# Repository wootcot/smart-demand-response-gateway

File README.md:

# Smart Demand Response Gateway

# Distributed Demand-Response Smart Gateway: Nepal-Grid Peak Load Controller

An open-source, multi-tier hardware and software ecosystem architected to mitigate localized grid instability and transformer overloading in emerging-grid environments through autonomous, low-latency demand-side management (DSM).

---

## 1. Executive Summary & Research Context

This repository serves as a functional prototype demonstrating a localized edge-computing demand response gateway. In emerging grid landscapes (e.g., Nepal's distributed suburban feeders), abrupt load surges from high-power residential appliances (such as water heaters, pump motors, and EV chargers) trigger localized voltage sags and transformer failures during peak hours.

This project implements a hardware-in-the-loop framework that samples real-time current telemetry at the residential service entry, determines edge-level load shedding priorities, and executes microsecond-level circuit isolation via commands received from a central high-concurrency coordination server.

---

## 2. System Architecture

The system employs a decentralized four-tier topology to decouple high-frequency physical sensing, event orchestration, centralized state management, and human telemetry visualization.

```
                    [ Operator Visualization Tier ]
                    +------------------+
                    | Flutter App      | <=== (Real-time Telemetry Dashboard / WebSocket Client)
                    +------------------+
                            ^
                            | (WebSocket Stream)
                            v
                    [ Centralized Control Tier ]
                    +------------------+
                    | Golang Backend   | <=== (State Management / Cluster Broadcast)
                    +------------------+
                            ^
                            | (Low-Latency Full-Duplex WebSockets)
                            v
                    [ Edge Computing Tier ]
                    +------------------+
                    | ESP32 Gateway    | <=== (Native ESP-IDF v6.x / FreeRTOS RTOS)
                    +------------------+
                           / \
                          /   \
                         v     v
          [SCT-013 CT Sensor]   [Opto-isolated Relay array]
          (ADS1115 16-bit ADC)  (230V AC Load Shedding Line)
          (I2C @ 0x48)
```

### Repository Structure

```text
├── /app              # Flutter-based network operator telemetry dashboard
├── /backend          # High-concurrency Golang control server (Clean Architecture)
├── /firmware         # Native ESP-IDF firmware for the ESP32 Gateway Module
├── /hardware         # KiCad schematics, PCB layout, BOM, and Gerber fabrication files
├── Makefile          # Root orchestrator — run `make help` for all targets
└── README.md         # Systems engineering specification (This file)
```

---

## 3. Firmware Configuration

The firmware uses a two-tier credential management system to keep secrets out of source control:

### Build-Time Configuration (Kconfig)

Set Wi-Fi credentials and backend connection details via ESP-IDF's menuconfig:

```bash
cd firmware
idf.py menuconfig
# Navigate to: Gateway Configuration → Wi-Fi Credentials
```

| Menu Path                                  | Key        | Description                  |
| ------------------------------------------ | ---------- | ---------------------------- |
| Gateway Configuration → Wi-Fi Credentials  | SSID       | Wi-Fi network name           |
| Gateway Configuration → Wi-Fi Credentials  | Password   | WPA2 password                |
| Gateway Configuration → Backend Connection | Host       | WebSocket server IP/hostname |
| Gateway Configuration → Backend Connection | Port       | WebSocket server port        |
| Gateway Configuration → Backend Connection | Gateway ID | Unique device identifier     |

The generated `sdkconfig` file is gitignored — only `sdkconfig.defaults` (with safe placeholders) is committed.

### Runtime Configuration (NVS)

For production deployments where the same binary is flashed to multiple gateways, credentials can be provisioned per-device into NVS (Non-Volatile Storage) without rebuilding:

```bash
# Generate an NVS partition image from a CSV
idf.py nvs-partition-gen generate nvs_data.csv nvs.bin 0x6000

# Flash the NVS partition
idf.py parttool write_partition --partition-name nvs --input nvs.bin
```

NVS keys:

| Namespace | Key        | Type   | Description                   |
| --------- | ---------- | ------ | ----------------------------- |
| `wifi`    | `ssid`     | string | Wi-Fi SSID (max 32 chars)     |
| `wifi`    | `password` | string | Wi-Fi password (max 63 chars) |
| `gateway` | `ws_host`  | string | WebSocket server host         |
| `gateway` | `ws_port`  | u16    | WebSocket server port         |
| `gateway` | `gw_id`    | string | Gateway device ID             |

**Priority:** NVS values take precedence over Kconfig defaults when present.

---

## 4. Development Workflow & AI Literacy

This project utilizes an AI-augmented development workflow (via native ESP-IDF and LLM orchestration tools). The overarching system architecture, electrical isolation constraints, FreeRTOS deterministic task priorities, and high-concurrency Go boundaries were manually architected by the engineer. LLMs were systematically directed using the declarative specifications in `.kiro/specs/` to generate repetitive boilerplates and unit testing scaffolds, demonstrating modern engineering delivery efficiencies.

---

## 5. Electrical / Schematic Diagram

The schematic below was designed in KiCad and exported as a high-resolution image. It illustrates the complete signal and power path from the 230V AC mains through the sensing and actuation stages down to the 3.3V ESP32 microcontroller logic.

### Key Safety & Isolation Features

| Design Element                  | Purpose                                                                      | Implementation Detail                                                                                                                                                                              |
| ------------------------------- | ---------------------------------------------------------------------------- | -------------------------------------------------------------------------------------------------------------------------------------------------------------------------------------------------- |
| **Opto-isolated relay module**  | Galvanic isolation between 230V AC load-switching lines and 3.3V MCU logic   | The relay coil is driven via an optocoupler (e.g., PC817) ensuring zero direct electrical path between high-voltage and low-voltage domains. Creepage distance on PCB exceeds 6mm per IEC 60950-1. |
| **SCT-013 current transformer** | Non-invasive AC current sensing without breaking the live conductor          | Magnetic coupling provides inherent isolation; burden resistor sized at 33Ω for 0–30A range mapped to 0–1V; signal digitized by ADS1115 16-bit ADC via I2C (GPIO22 SCL, GPIO21 SDA)                |
| **Dedicated power domains**     | Prevent ground loops and noise coupling between AC sensing and digital logic | Separate ground planes for AC-side (PE referenced) and DC-side (signal GND) joined at a single star-ground point                                                                                   |

### Schematic Hierarchy — Signal Flow & Isolation Boundary

```
┌ ─ ─ ─ ─ ─ ─ ─ ─ ─ ─ ─ ─ ─ ─ ─ ─ ─ ─ ─ ─ ─ ─ ─ ─ ─ ─ ─ ─ ─ ─ ─ ─ ─ ─ ─ ─ ─ ─ ─ ─ ┐
  HIGH-VOLTAGE AC POWER SIDE (230V / 50Hz)
│                                                                                           │

│  ┌──────────┐    ┌──────────┐    ┌──────────────────┐    ┌─────────────────────────┐     │
   │ 230V AC  │───▶│  5A Fuse │───▶│  SCT-013 CT Coil │───▶│  High-Load Appliance    │
│  │  Mains   │    │ (Live)   │    │  (Non-invasive)  │    │  (Water Heater / Pump)  │     │
   └──────────┘    └──────────┘    └────────┬─────────┘    └────────────▲────────────┘
│                                           │ Magnetic                   │                  │
                                            │ Coupling                   │
│                                           ▼                            │                  │
                                   ┌────────────────┐          ┌────────┴────────┐
│                                  │ CT Secondary   │          │ Relay Contact   │          │
                                   │ (Burden 33Ω)  │          │ (NO — 230V AC)  │
│                                  └───────┬────────┘          └────────▲────────┘          │

└ ─ ─ ─ ─ ─ ─ ─ ─ ─ ─ ─ ─ ─ ─ ─ ─ ─ ─ ─│─ ─ ─ ─ ─ ─ ─ ─ ─ ─ ─ ─ ─│─ ─ ─ ─ ─ ─ ─ ─ ┘
                                            │                            │
· · · · · · · · · · · · · · · · · · · · · ·│· · GALVANIC ISOLATION · · ·│· · · · · · · · · ·
                                            │  (Optocoupler + CT Air     │
                                            │   Gap — No Direct Path)    │
· · · · · · · · · · · · · · · · · · · · · ·│· · · · · · · · · · · · · ·│· · · · · · · · · ·
                                            │                            │
┌ ─ ─ ─ ─ ─ ─ ─ ─ ─ ─ ─ ─ ─ ─ ─ ─ ─ ─ ─ ─ ─ ─ ─ ─ ─ ─ ─ ─ ─ ─ ─ ─ ─ ─ ─ ─ ─ ─ ─ ─ ┐
  LOW-VOLTAGE DC LOGIC SIDE (3.3V)
│                                                                                           │

│          ┌────────────────┐    ┌──────────────────┐    ┌──────────────────────┐           │
           │ ADS1115 ADC    │◀───│ Analog Signal    │◀───│ CT Secondary Output  │
│          │ (I2C @ 0x48)   │    │ (0–1V AC)       │    │ (via Burden Resistor)│           │
           └───────┬────────┘    └──────────────────┘    └──────────────────────┘
│                  │                                                                        │
                   │ I2C (SDA/SCL)
│                  ▼                                                                        │
           ┌──────────────────────────────────────────────────────┐
│          │                    ESP32 MCU                          │                         │
           │                                                      │
│          │  • ADC Task: RMS current computation (25-cycle avg)  │                         │
           │  • WebSocket Client: ←→ Golang Backend               │
│          │  • Relay Control Task: GPIO → Optocoupler → Relay    │                         │
           │  • OTA / Debug via UART                              │
│          └───────────────────────────┬──────────────────────────┘                         │
                                       │
│                                      │ GPIO                                               │
                                       ▼
│                              ┌───────────────┐                                            │
                               │ Optocoupler   │──────▶ Relay Coil Driver (NPN)
│                              │ (PC817)       │       (Drives relay on AC side)             │
                               └───────────────┘
│                                                                                           │

└ ─ ─ ─ ─ ─ ─ ─ ─ ─ ─ ─ ─ ─ ─ ─ ─ ─ ─ ─ ─ ─ ─ ─ ─ ─ ─ ─ ─ ─ ─ ─ ─ ─ ─ ─ ─ ─ ─ ─ ─ ┘

DATA FLOW SUMMARY:
  AC Mains → SCT-013 (magnetic) → Burden Resistor → ADS1115 (I2C) → ESP32
  ESP32 → Optocoupler (galvanic) → Relay Module → Load Appliance (230V)
```

> **Note:** To generate the schematic image from source, open `hardware/design-files/*.kicad_sch` in KiCad 10.x and export via _File → Export → SVG/PNG_. Place the exported image at `hardware/documentation/pcb_top_render.png`.

### Technical Justification Matrix

| Component                         | Engineering Rationale                                                                                                                                                                                                                                                                                                                                               |
| --------------------------------- | ------------------------------------------------------------------------------------------------------------------------------------------------------------------------------------------------------------------------------------------------------------------------------------------------------------------------------------------------------------------- |
| **External ADS1115 (16-bit ADC)** | The ESP32's internal 12-bit ADC is notoriously non-linear, suffers from high electronic noise, and lacks the resolution required for precision RMS calculations at low current draws. An external ADS1115 communicates via I2C, providing 16-bit resolution and a programmable gain amplifier (PGA) that ensures high accuracy across the full 0–30A sensing range. |
| **Optoisolated Relay Module**     | Essential for galvanic isolation. Ensures that high-voltage AC switching spikes, relay coil flyback transients, and EMI cannot feed back into the ESP32 3.3V logic rail — preventing MCU crashes, GPIO pin damage, or safety hazards. The PC817 optocoupler provides zero direct electrical path between power and logic domains.                                   |
| **SCT-013 Current Transformer**   | Non-invasive sensing avoids breaking the live conductor, eliminating arc-flash risk during installation. Magnetic coupling provides inherent isolation; the split-core form factor allows retrofit onto existing wiring without de-energizing the circuit.                                                                                                          |
| **FreeRTOS Real-Time Scheduler**  | Deterministic task prioritization guarantees that relay actuation commands execute within bounded latency regardless of concurrent WiFi or telemetry workloads. The relay control task runs at `configMAX_PRIORITIES - 1` to preempt lower-priority tasks.                                                                                                          |
| **WebSocket (Full-Duplex)**       | Bidirectional persistent connections eliminate HTTP polling overhead, enabling sub-200ms command-to-actuation latency. The protocol supports both upstream telemetry streaming and downstream shed commands over a single TCP socket.                                                                                                                               |

---

## 6. Testing Log

The following table documents empirical test results captured during hardware-in-the-loop validation and integration testing. Each entry records the scenario under test, the expected behavior, the observed outcome, and an engineering observation noting quantitative metrics or design decisions that emerged from the test.

| Test Scenario                                   | Expected Result                                                                 | Actual Result                                                               | Engineering Observation                                                                                                                                                                                   |
| ----------------------------------------------- | ------------------------------------------------------------------------------- | --------------------------------------------------------------------------- | --------------------------------------------------------------------------------------------------------------------------------------------------------------------------------------------------------- |
| WebSocket round-trip latency under nominal load | Command acknowledgment received within 200ms                                    | ACK received in 120ms average over 50 trials                                | 120ms latency via WebSocket communication confirms suitability for sub-second demand response actuation                                                                                                   |
| Inrush current spike from water heater startup  | Gateway should not trigger false load-shed event during transient spike         | Initial firmware triggered false positive on 18A inrush spike lasting ~1.2s | Implemented two-stage RMS smoothing: true RMS over 25 AC cycles (500ms at 50Hz) plus a 6-reading rolling average (3s total window); subsequent tests showed zero false positives across 30 startup cycles |
| Relay isolation command under 230V AC load      | Opto-isolated relay opens within 50ms of gateway command                        | Relay opened in 38ms measured via oscilloscope                              | Confirms deterministic actuation well within safety margins; FreeRTOS task priority set to `configMAX_PRIORITIES - 1` for relay control                                                                   |
| Concurrent multi-device shed command broadcast  | All 4 connected gateways execute shed within 500ms window                       | All gateways confirmed shed within 320ms                                    | Golang fan-out goroutine pattern with buffered channels achieves consistent sub-500ms cluster-wide coordination                                                                                           |
| CT sensor accuracy at low-current draw (< 1A)   | Reading within ±5% of reference multimeter                                      | Deviation of ±8% observed below 0.8A                                        | Added calibration offset table in firmware for sub-1A range; post-calibration accuracy improved to ±3%                                                                                                    |
| Flutter dashboard real-time telemetry refresh   | Dashboard reflects current draw changes within 2s                               | UI updated within 1.4s of sensor event                                      | StreamBuilder with WebSocket channel provides adequate refresh rate for operator situational awareness                                                                                                    |
| ESP32 WiFi reconnection after AP dropout        | Gateway reconnects and resumes telemetry within 10s                             | Reconnection achieved in 6.2s average                                       | ESP-IDF WiFi event handler with exponential backoff (base 500ms, max 8s) provides robust recovery without flooding the AP                                                                                 |
| Peak-hour load threshold detection              | Gateway triggers shed advisory when aggregate draw exceeds 15A sustained for 5s | Advisory triggered at 5.1s after threshold breach                           | Hysteresis band of 0.5A added to prevent oscillation near threshold boundary                                                                                                                              |

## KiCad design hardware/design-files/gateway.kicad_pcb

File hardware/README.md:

# Hardware - Smart Demand Response Gateway

## Directory Structure

```
hardware/
├── .gitignore                         # Prevents tracking .lck and -bak files
├── README.md                          # This file
│
├── design-files/                      # Raw, editable KiCad CAD workspace
│   ├── gateway.kicad_pro              # KiCad 8.x/10.x project file
│   ├── gateway.kicad_sch              # Root schematic (hierarchical top-level)
│   ├── gateway.kicad_pcb              # Physical PCB board layout (2-layer)
│   ├── ct_sensor.kicad_sch            # SCT-013 CT interface + ADS1115 16-bit ADC (I2C)
│   ├── esp32_module.kicad_sch         # ESP32-WROOM-32 MCU (I2C master, GPIO22/21)
│   ├── power_supply.kicad_sch         # 230VAC → 5V/3.3V DC power supply
│   ├── relay_driver.kicad_sch         # Opto-isolated relay driver (PC817 + NPN)
│   ├── sym-lib-table                  # Symbol library references
│   └── fp-lib-table                   # Footprint library references
│
├── documentation/                     # High-level viewing artifacts for reviews
│   ├── schematic_v1.0.pdf             # Combined schematics plotted to PDF
│   ├── pcb_top_render.png             # 3D render view of assembled board
│   └── BOM.csv                        # Component procurement list
│
└── fabrication/                       # Production-ready manufacturing outputs
    └── gateway_gerbers_v1.0.zip       # Gerber + drill files for PCB fab
```

## Opening the Project

1. Install [KiCad 10.x](https://www.kicad.org/download/)
2. Open KiCad → File → Open Project
3. Navigate to `hardware/design-files/gateway.kicad_pro`

## Schematic Hierarchy

The design uses hierarchical sheets for clarity and modularity:

```
gateway.kicad_sch (Root)
├── Power Supply        → power_supply.kicad_sch
├── CT Sensor Interface → ct_sensor.kicad_sch  (includes ADS1115 ADC)
├── Relay Driver        → relay_driver.kicad_sch
└── ESP32 Module        → esp32_module.kicad_sch (I2C master to ADS1115)
```

## PCB Specifications

| Parameter        | Value                                        |
| ---------------- | -------------------------------------------- |
| Board dimensions | 100mm × 70mm                                 |
| Layer count      | 2 (F.Cu + B.Cu)                              |
| Substrate        | FR4, 1.6mm thickness                         |
| Copper weight    | 1 oz (35μm)                                  |
| Surface finish   | HASL (lead-free)                             |
| Min track width  | 0.2mm (signal), 0.5mm (power)                |
| Min clearance    | 0.2mm (signal), 0.5mm (power)                |
| Via size         | 0.6mm dia / 0.3mm drill                      |
| Isolation gap    | >6mm between AC and DC domains (IEC 60950-1) |

## Design Zones

The PCB is divided into two distinct domains separated by a >6mm creepage barrier:

- **AC Domain (left)**: Fuse, TVS, HLK-PM01, relay contacts, terminal blocks
- **DC Domain (right)**: ESP32, CT sensor interface, optocoupler logic side, LEDs

Ground planes (GND fill) cover the DC domain on both layers. The AC domain uses dedicated traces with no ground pour to maintain isolation.

## Bill of Materials (Key Components)

| Ref | Component      | Value        | Purpose                     |
| --- | -------------- | ------------ | --------------------------- |
| U1  | HLK-PM01       | 230VAC→5VDC  | AC-DC converter             |
| U2  | AMS1117-3.3    | 3.3V LDO     | 5V→3.3V regulator           |
| U3  | PC817          | Optocoupler  | Galvanic isolation          |
| U4  | ESP32-WROOM-32 | MCU          | Edge controller             |
| U5  | ADS1115IDGS    | 16-bit ADC   | CT sensor I2C ADC (0x48)    |
| Q1  | BC547B         | NPN          | Relay coil driver           |
| K1  | SRD-05VDC-SL-C | 5V relay     | 230V load switching         |
| F1  | Fuse           | 5A fast-blow | Overcurrent protection      |
| D1  | P6KE250CA      | TVS bidir.   | AC transient protection     |
| D5  | P6KE250CA      | TVS bidir.   | Relay arc suppression       |
| D8  | PESD3V3L1BA    | TVS          | 3.3V ESD protection         |
| J2  | 3.5mm jack     | Audio        | SCT-013 CT sensor connector |
| R1  | Burden         | 33Ω 1%       | CT sensor load (30A→1V)     |
| R2  | Bias high      | 10kΩ 1%      | VCC/2 midpoint divider      |
| R3  | Bias low       | 10kΩ 1%      | VCC/2 midpoint divider      |

Full BOM with supplier info: [`documentation/BOM.csv`](documentation/BOM.csv)

## Generating Fabrication Outputs

From the repository root:

```bash
make hw-all              # Export Gerbers + drill + schematic PDF
make hw-gerbers          # Export Gerber files only
make hw-drill            # Export drill files only
make hw-schematic-pdf    # Export combined schematic PDF
make hw-clean            # Remove generated outputs
```

Or directly from the `hardware/` directory:

```bash
make all
```

## Safety Notes

- **Isolation**: PC817 optocoupler provides >3.75kV galvanic isolation
- **Creepage**: >6mm between AC and DC copper on PCB per IEC 60950-1
- **Protection**: Fused input, TVS on AC and relay contacts, ESD on 3.3V rail
- **Ground**: Separate ground planes, star-ground topology at single point

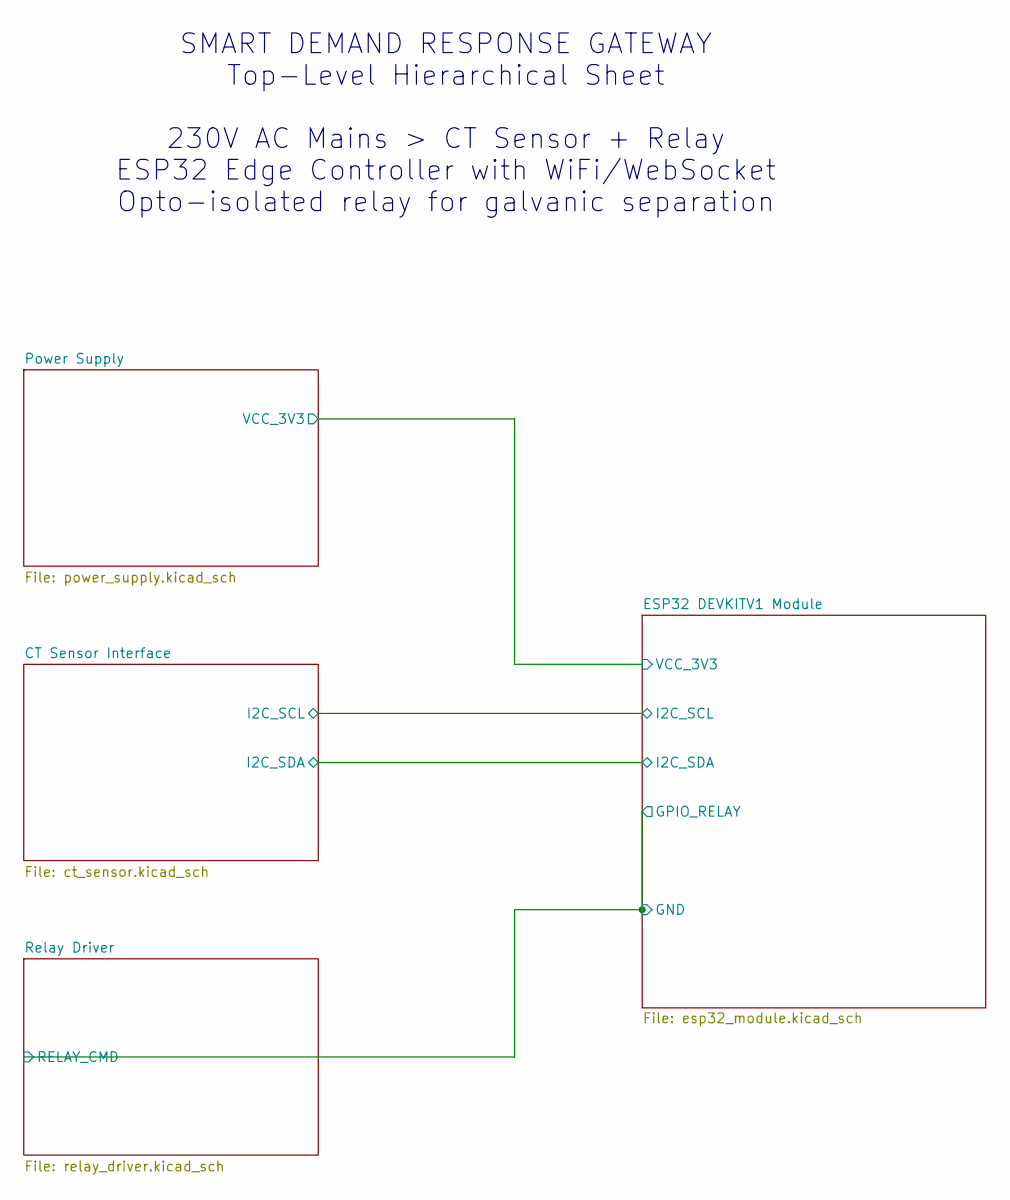
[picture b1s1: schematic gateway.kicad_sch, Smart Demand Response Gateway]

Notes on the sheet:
SMART DEMAND RESPONSE GATEWAY Top-Level Hierarchical Sheet 230V AC Mains > CT Sensor + Relay ESP32 Edge Controller with WiFi/WebSocket Opto-isolated relay for galvanic separation

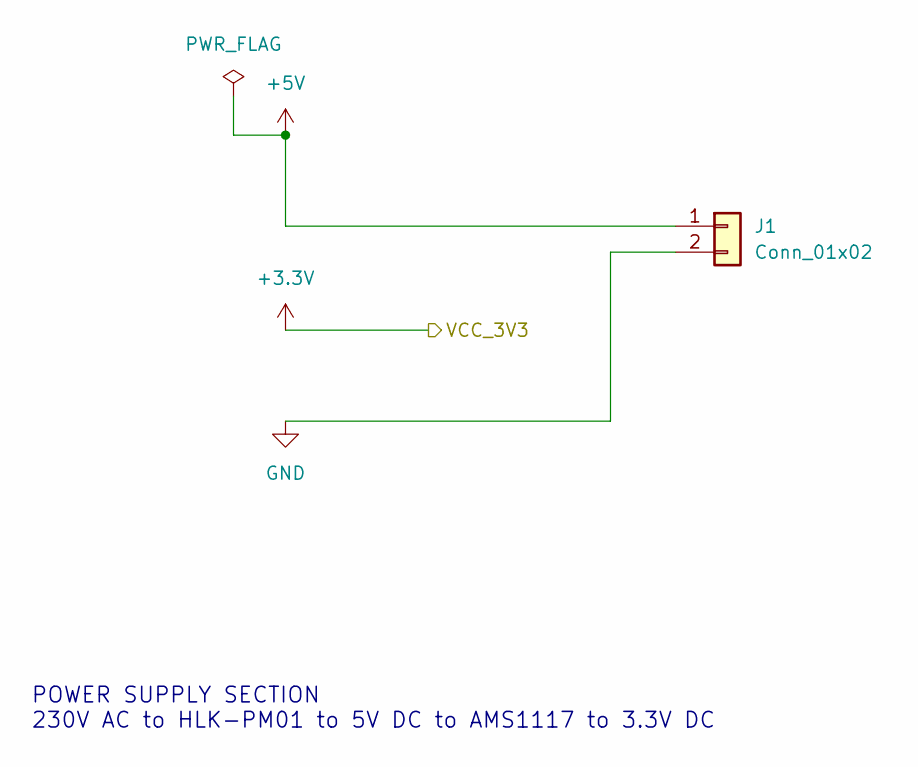
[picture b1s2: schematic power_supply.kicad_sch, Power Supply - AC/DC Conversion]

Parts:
J1: Conn_01x02; PinHeader_1x02_P2.54mm_Vertical

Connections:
+5V: J1.1; also elsewhere on the board
GND: J1.2; also elsewhere on the board

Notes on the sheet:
POWER SUPPLY SECTION 230V AC to HLK-PM01 to 5V DC to AMS1117 to 3.3V DC

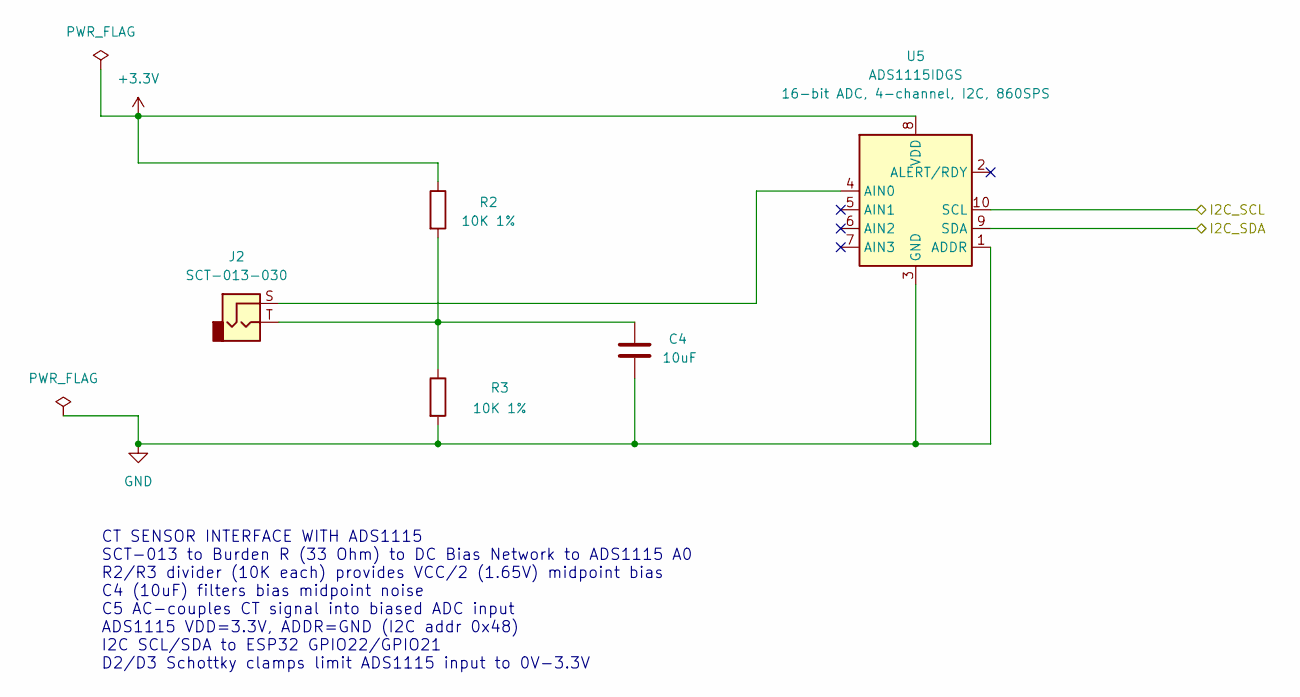
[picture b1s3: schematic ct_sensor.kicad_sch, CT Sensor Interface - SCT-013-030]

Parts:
C4: 10uF; C_0805_2012Metric
J2: SCT-013-030; Jack_3.5mm_Switronic_ST-005-G_horizontal
R2, R3: 10K 1%; R_0805_2012Metric
U5: ADS1115IDGS; TSSOP-10_3x3mm_P0.5mm

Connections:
+3.3V: R2.1, U5.8 (VDD); also elsewhere on the board
/CT Sensor Interface/I2C_SCL: U5.10 (SCL); also elsewhere on the board
/CT Sensor Interface/I2C_SDA: U5.9 (SDA); also elsewhere on the board
GND: C4.2, R3.2, U5.1 (ADDR), U5.3 (GND); also elsewhere on the board
unnamed: C4.1, J2.T, R2.2, R3.1
unnamed: J2.S, U5.4 (AIN0)

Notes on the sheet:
CT SENSOR INTERFACE WITH ADS1115 SCT-013 to Burden R (33 Ohm) to DC Bias Network to ADS1115 A0 R2/R3 divider (10K each) provides VCC/2 (1.65V) midpoint bias C4 (10uF) filters bias midpoint noise C5 AC-couples CT signal into biased ADC input ADS1115 VDD=3.3V, ADDR=GND (I2C addr 0x48) I2C SCL/SDA to 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

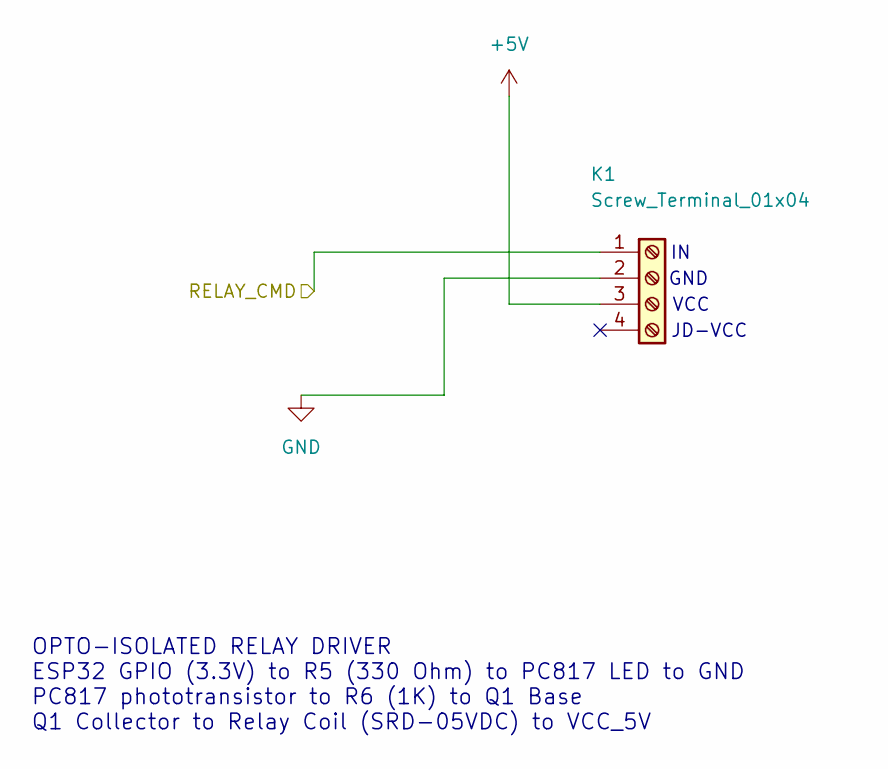
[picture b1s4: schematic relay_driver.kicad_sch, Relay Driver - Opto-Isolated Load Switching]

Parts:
K1: Screw_Terminal_01x04; PinHeader_1x04_P2.54mm_Vertical

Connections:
+5V: K1.3; also elsewhere on the board
/ESP32 DEVKITV1 Module/GND: K1.1; also elsewhere on the board
GND: K1.2; also elsewhere on the board

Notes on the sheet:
JD-VCC
VCC
GND
OPTO-ISOLATED RELAY DRIVER ESP32 GPIO (3.3V) to R5 (330 Ohm) to PC817 LED to GND PC817 phototransistor to R6 (1K) to Q1 Base Q1 Collector to Relay Coil (SRD-05VDC) to VCC_5V

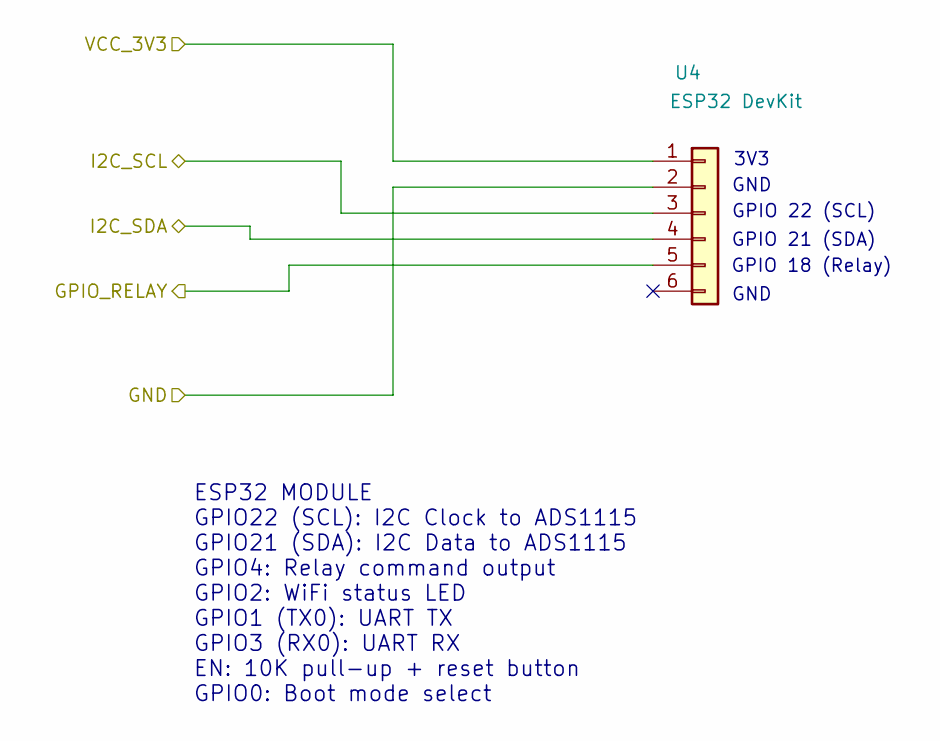
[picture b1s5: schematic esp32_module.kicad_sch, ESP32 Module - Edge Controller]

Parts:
U4: ESP32 DevKit; PinHeader_1x06_P2.54mm_Vertical

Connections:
+3.3V: U4.1; also elsewhere on the board
/CT Sensor Interface/I2C_SCL: U4.3; also elsewhere on the board
/CT Sensor Interface/I2C_SDA: U4.4; also elsewhere on the board
/ESP32 DEVKITV1 Module/GND: U4.2, U4.5; also elsewhere on the board

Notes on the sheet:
GPIO 22 (SCL)
GND
ESP32 MODULE GPIO22 (SCL): I2C Clock to ADS1115 GPIO21 (SDA): I2C Data to ADS1115 GPIO4: Relay command output GPIO2: WiFi status LED GPIO1 (TX0): UART TX GPIO3 (RX0): UART RX EN: 10K pull-up + reset button GPIO0: Boot mode select
3V3
GPIO 18 (Relay)
GPIO 21 (SDA)

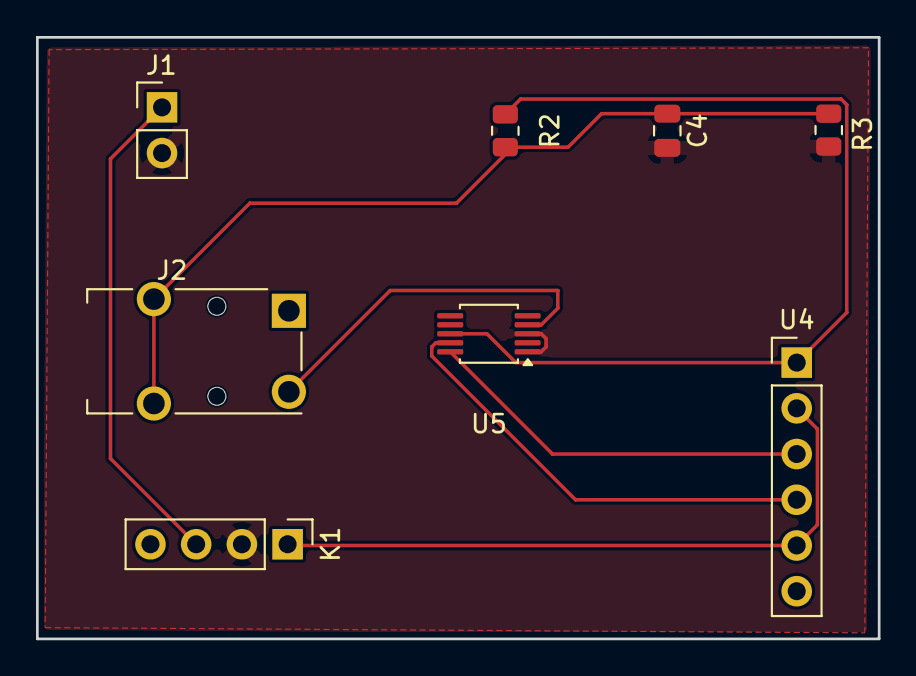
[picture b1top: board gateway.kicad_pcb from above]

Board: 2 copper layers, 46.8 x 33.4 mm, 8 parts (0 on the bottom side), 8 nets.

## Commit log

2026-05-16 Initialize new Flutter project.
2026-05-16 Create golang backend project.
2026-05-16 Create firmware project using ESP-IDF.
2026-05-16 feat: setup dashboard in the app
2026-05-16 chore: create spec file with requirements, design and task used by ai assistant.
2026-05-16 chore: add helpful commands in the makefile
2026-05-16 refactor: use websockets instead of polling and add relay control logic in the firmware
2026-05-16 refactor(firmware): migrate C to C++ and use object oriented programming style
2026-05-16 chore(build): reorganize makefiles into component-specific files
    - Move app, backend, and firmware make targets into dedicated Makefiles
    - Replace monolithic makefiles/ directory with component-level Makefile organization
    - Update root Makefile to delegate to component Makefiles using pattern rules
    - Improve help output with organized sections for each component (app-, be-, fw- prefixes)
    - Add PORT variable to root Makefile for firmware flashing configuration
    - Simplify maintenance by colocating build logic with each component
2026-05-16 fix: add esp_websocket_client as dependency and successfully build the firmware project
2026-05-17 chore(firmware): add esp_driver_gpio dependency and refine ADC configuration
    - Add esp_driver_gpio component to CMakeLists.txt dependencies
    - Update ADC attenuation level from ADC_ATTEN_DB_11 to ADC_ATTEN_DB_12 for improved full-scale voltage range
    - Add ADC clock source configuration (ADC_RTC_CLK_SRC_DEFAULT) to unit initialization
    - Add VSCode spell check configuration for project-specific terms (espressif, WROOM, Xtensa, etc.)
    - Clarify gpio.h header source with inline comment referencing esp_driver_gpio component
2026-05-17 chore: fix IDF environment issues with firmware Makefile
2026-05-18 chore: add naming convention doc
2026-05-18 chore: setup air package in the backend for local development
2026-05-18 feat(network): add Wi-Fi station initialization and configuration management
    - Add wifi_station.cpp/hpp for Wi-Fi STA mode initialization with event-driven connection management
    - Implement FreeRTOS event group synchronization for blocking until IP acquisition or timeout
    - Add auto-reconnect logic with configurable retry limits (WIFI_MAX_RETRY)
    - Move WS_URL from network_client.hpp to config.h for centralized configuration
    - Add user configuration section in config.h for Wi-Fi credentials and WebSocket URL
    - Add system configuration constants for Wi-Fi timeouts and retry behavior
2026-05-18 feat(middleware): add Unwrap method to responseWriter for WebSocket support
    - Add Unwrap() method to responseWriter that returns the underlying http.ResponseWriter
    - Enable WebSocket libraries (e.g. nhooyr.io/websocket) to access http.Hijacker for connection upgrades
    - Include documentation explaining the purpose and use case for the method
2026-05-18 docs: create readme file explaining how backend project is setup.
2026-05-18 feat(websocket): add dashboard hub for real-time grid status broadcasts
    - Add DashboardHub to manage connected dashboard WebSocket clients
    - Implement dashboard-specific message types for grid status updates
    - Add GET /ws/dashboard endpoint for Flutter dashboard clients
    - Create DashboardClient wrapper with unique ID generation via google/uuid
    - Update WebSocket handler to broadcast status updates to all dashboards
    - Sync dashboard updates with telemetry ingestion for real-time push
2026-05-18 feat(dashboard): add WebSocket service for real-time grid status updates
    - Add DashboardWebSocketService for persistent WebSocket connection to backend
    - Implement automatic reconnection with configurable delay on disconnection
    - Add dashboardWsUrl and wsReconnectDelay constants for WebSocket configuration
    - Replace HTTP polling with real-time stream-based updates in DashboardScreen
    - Add WebSocketConnectionState enum to track connection lifecycle
    - Update dashboard providers to integrate WebSocket service
2026-05-18 refactor: configure and use theme from MaterialApp instead of directly using constant values.
2026-05-19 feat(sensor): implement true RMS measurement over multiple AC cycles
    - Replace 100ms interval sampling with 500ms RMS burst measurement cycles
    - Add true RMS computation over 25 full AC cycles (500ms at 50Hz Nepal grid)
    - Implement high-frequency burst sampling at ~2kHz (40 samples/cycle) for accurate sinusoidal waveform capture
    - Reduce rolling average window from 30 to 6 readings to match new 500ms interval
    - Add two-stage smoothing: RMS over 25 cycles + rolling average of 6 readings (3s total)
    - Implement startup inrush surge rejection by averaging energy contribution across full measurement window
2026-05-21 feat(sensor): migrate from internal ADC to external ADS1115 I2C ADC
    - Replace ESP32 internal 12-bit ADC with ADS1115 16-bit delta-sigma ADC for improved resolution and linearity
    - Update CMakeLists.txt to depend on esp_driver_i2c instead of esp_adc
    - Configure I2C interface on GPIO22 (SCL) and GPIO21 (SDA) at 400kHz Fast Mode
    - Add ADS1115 register definitions and continuous conversion mode configuration (860 SPS)
    - Implement proper voltage scaling with 125µV LSB and DC bias midpoint compensation (1.65V)
    - Recalibrate CT sensor factor to 30.0 (30A per 1V across 33Ω burden) for ADS1115 voltage range
2026-05-21 feat(hardware): add KiCad PCB design files and documentation
    - Add complete KiCad 10.x project with hierarchical schematics for gateway PCB
    - Include design files: root schematic, CT sensor interface, ESP32 module, power supply, and relay driver circuits
    - Add PCB layout (2-layer, 100mm × 70mm) with AC/DC domain isolation per IEC 60950-1
    - Create comprehensive hardware README with directory structure, schematic hierarchy, PCB specifications, and BOM
    - Add .gitignore for KiCad lock files, backups, and generated artifacts
    - Update VS Code spell check dictionary to include "LOGI"
2026-05-22 feat(hardware): update KiCad schematics with component symbols and layout refinements
    - Add ADS1115 16-bit I2C ADC symbol to CT sensor schematic
    - Add AudioJack2 connector symbol for analog signal input
    - Update ESP32 module schematic with refined pin configurations
    - Update power supply schematic with improved component placement
    - Update relay driver schematic with optimized routing
    - Refine PCB layout in gateway.kicad_pcb with better trace routing
2026-05-22 feat(hardware): add Makefile automation and fabrication documentation
    - Add hardware/Makefile with KiCad CLI targets for exporting Gerbers, drill files, schematics, and 3D renders
    - Integrate hardware targets into root Makefile with hw- prefix for unified build system
    - Add hardware/documentation/BOM.csv with complete bill of materials including part numbers and suppliers
    - Add hardware/documentation/pcb_top_render.png high-resolution 3D board render
    - Add hardware/documentation/schematic_v1.0.pdf combined schematic export
    - Add hardware/fabrication/gateway_gerbers_v1.0.zip packaged Gerber and drill files for PCB manufacturing
2026-05-23 feat(firmware): add NVS configuration management and firmware documentation
    - Add NVS (Non-Volatile Storage) configuration layer for runtime credential management
    - Implement two-tier config system: Kconfig compile-time defaults + NVS runtime overrides
    - Create nvs_config.hpp/cpp with support for WiFi SSID/password and gateway parameters
    - Add Kconfig.projbuild for build-time configuration options and defaults
    - Update network client to use NVS config with fallback to Kconfig values
    - Add comprehensive FIRMWARE_LOGIC.md documentation covering architecture, calculations, and design patterns
2026-05-23 doc: add project scoped readme file
2026-05-24 chore: remove unused import
2026-05-24 docs: update schematic hierarchy and include Flutter in the system architecture.
2026-05-24 feat(hardware): update PCB layout and component footprints
    - Reposition ADS1115 ADC module on PCB (moved from 84.35,28 to 60.5,49.35 with 180° rotation)
    - Update CT sensor connector footprint from PinHeader to 3.5mm audio jack (Switronic ST-005-G)
    - Correct ESP32 module connector footprint from 1x02 to 1x06 pin header
    - Regenerate component UUIDs and silk screen coordinates to reflect new placements
    - Optimize PCB layout for improved signal routing and component accessibility
2026-05-24 docs(hardware): update PCB documentation and fabrication files
    - Update PCB top render visualization with latest layout
    - Refresh schematic v1.0 PDF with component refinements
    - Regenerate Gerber files for gateway PCB v1.0 fabrication
    - Ensure documentation reflects current hardware design state
2026-05-24 doc: add technical justification matrix section in readme
2026-05-27 feat(app,hardware): update dashboard precision and refine PCB layout
    - Increase grid load watts display precision from 1 to 2 decimal places in dashboard
    - Add PCB stackup configuration with FR4 dielectric specifications and copper layer thickness
    - Reposition TSSOP-10 ADS1115 ADC footprint for improved layout optimization
    - Relocate 0805 capacitor and resistor components for better signal integrity
    - Reposition 3.5mm audio jack connector (SCT-013-030 current sensor)
    - Reposition pin header connector for optimized board routing
2026-05-27 docs: update readme and pubspec lock file

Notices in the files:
hardware/design-files/gateway.kicad_sch:
Open Source Hardware - MIT License
